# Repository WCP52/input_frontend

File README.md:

input_frontend
==============

Gain/Phase analyzer input frontend

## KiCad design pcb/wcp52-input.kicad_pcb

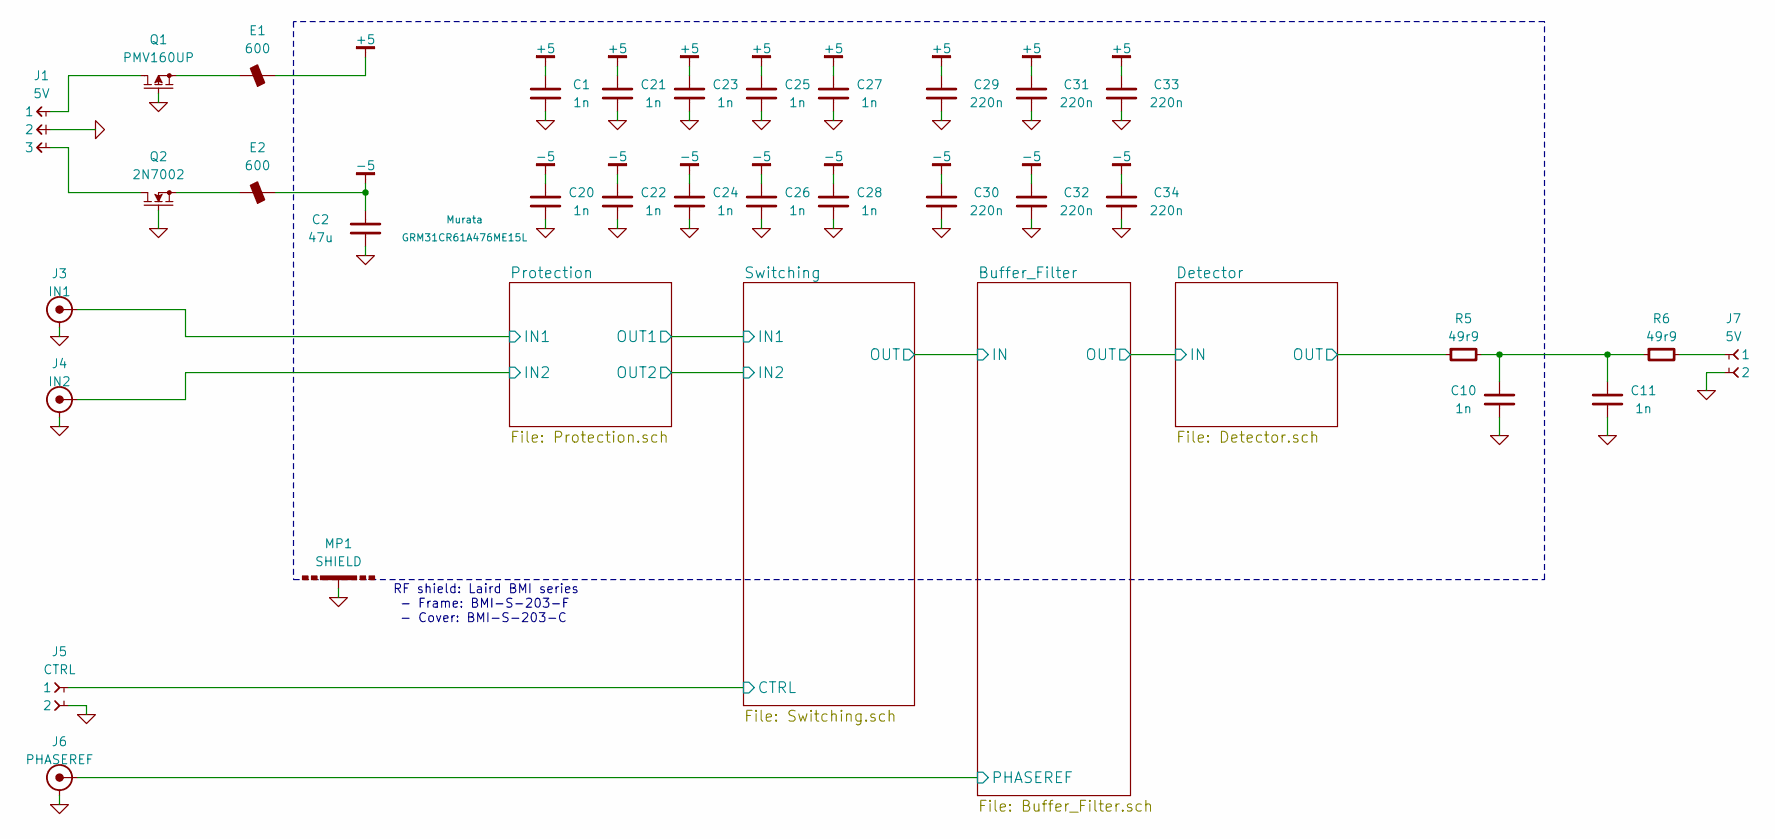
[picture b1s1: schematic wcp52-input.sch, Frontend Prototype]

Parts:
C1, C10, C11, C20, C21, C22, C23, C24, C25, C26, C27, C28: 1n; CAPC1005X55
C2: 47u; CAPC3216X70
C29, C30, C31, C32, C33, C34: 220n; CAPC2012X70
E1, E2: 600; INDC1005X60
J1: 5V; CONN_3-SIL
J3: IN1; CONN-2_CONSMA001
J4: IN2; CONN-2_CONSMA001
J5: CTRL; CONN_2-SIL
J6: PHASEREF; CONN-2_CONSMA001
J7: 5V; CONN_2-SIL
MP1: SHIELD
Q1: PMV160UP; SOT-23
Q2: 2N7002; SOT-23
R5, R6: 49r9; RESC1005X40

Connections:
+5: C1.1, C21.1, C23.1, C25.1, C27.1, C29.1, C31.1, C33.1, E1.2; also elsewhere on the board
-5: C2.1, C20.1, C22.1, C24.1, C26.1, C28.1, C30.1, C32.1, C34.1, E2.2; also elsewhere on the board
/Buffer_Filter/PHASEREF: J6.1; also elsewhere on the board
/Detector/OUT: R5.1; also elsewhere on the board
/Protection/IN1: J3.1; also elsewhere on the board
/Protection/IN2: J4.1; also elsewhere on the board
/Switching/CTRL: J5.1; also elsewhere on the board
GND: C1.2, C2.2, C10.2, C11.2, C20.2, C21.2, C22.2, C23.2, C24.2, C25.2, C26.2, C27.2, C28.2, C29.2, C30.2, C31.2, C32.2, C33.2, C34.2, J1.2, J3.2, J4.2, J5.2, J6.2, J7.2, MP1.1, Q1.1, Q2.1; also elsewhere on the board
unnamed: C10.1, C11.1, R5.2, R6.1
unnamed: E1.1, Q1.2
unnamed: E2.1, Q2.2
unnamed: J1.1, Q1.3
unnamed: J1.3, Q2.3
unnamed: J7.1, R6.2

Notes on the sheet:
RF shield: Laird BMI series - Frame: BMI-S-203-F - Cover: BMI-S-203-C

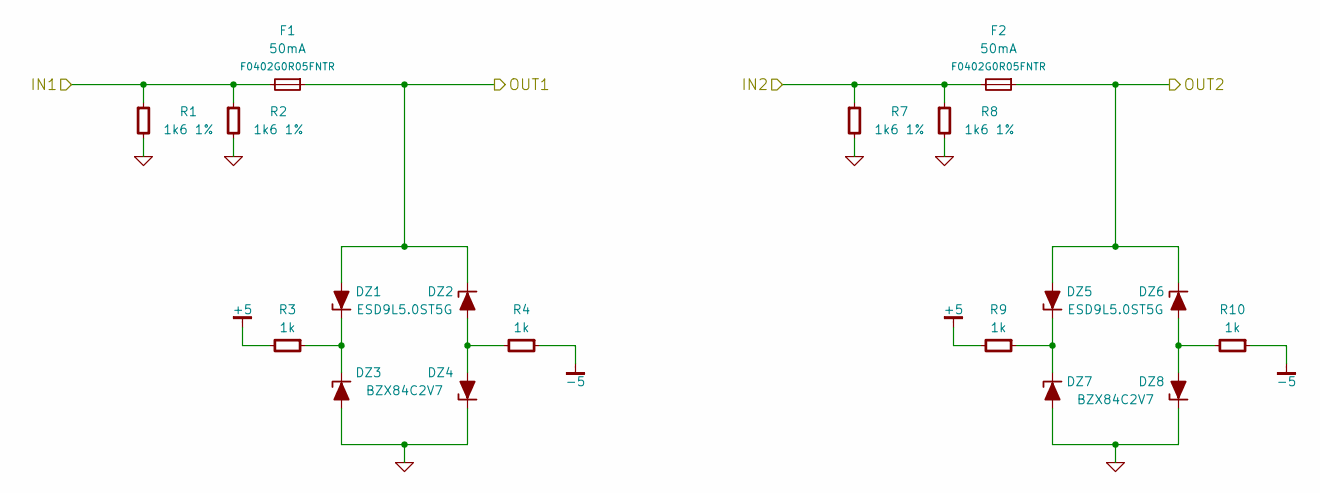
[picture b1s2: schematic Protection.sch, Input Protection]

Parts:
DZ1, DZ2, DZ5, DZ6: ESD9L5.0ST5G; SOD-923
DZ3, DZ4, DZ7, DZ8: BZX84C2V7; SOT-23
F1, F2: 50mA; RESC1005X40
R1, R2, R7, R8: 1k6 1%; RESC1005X40
R3, R4, R9, R10: 1k; RESC1005X40

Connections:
+5: R3.2, R9.2; also elsewhere on the board
-5: R4.1, R10.1; also elsewhere on the board
/Protection/IN1: F1.2, R1.1, R2.1; also elsewhere on the board
/Protection/IN2: F2.2, R7.1, R8.1; also elsewhere on the board
/Switching/IN1: DZ1.2, DZ2.1, F1.1; also elsewhere on the board
/Switching/IN2: DZ5.2, DZ6.1, F2.1; also elsewhere on the board
GND: DZ3.1, DZ4.3, DZ7.1, DZ8.3, R1.2, R2.2, R7.2, R8.2; also elsewhere on the board
unnamed: DZ1.1, DZ3.3, R3.1
unnamed: DZ2.2, DZ4.1, R4.2
unnamed: DZ5.1, DZ7.3, R9.1
unnamed: DZ6.2, DZ8.1, R10.2

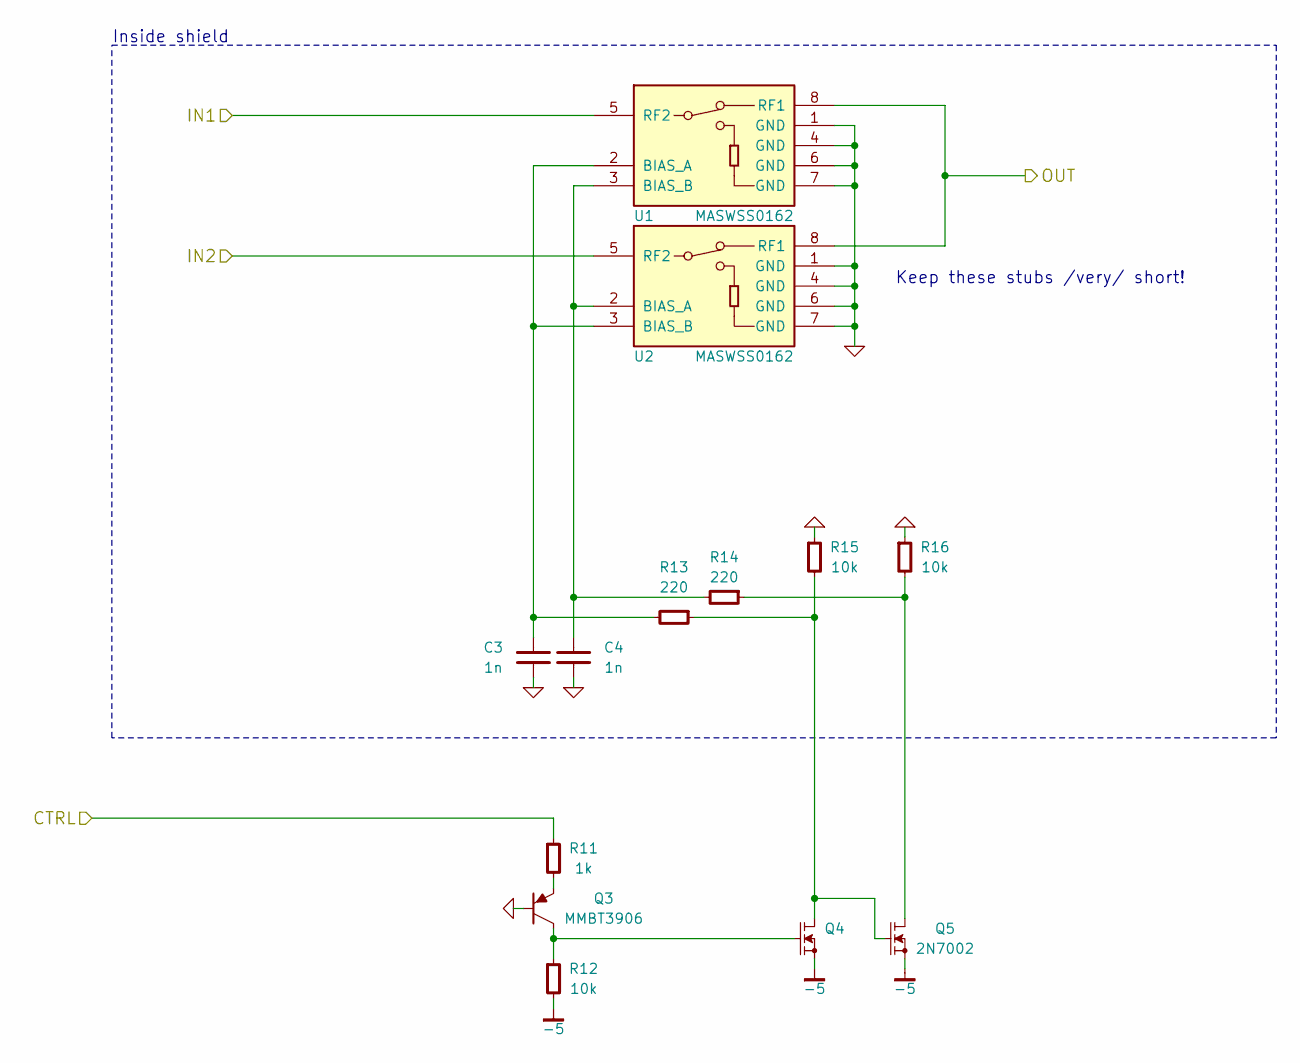
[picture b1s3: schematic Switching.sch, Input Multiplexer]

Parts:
C3, C4: 1n; CAPC1005X55
Q3: MMBT3906; SOT-23
Q4, Q5: 2N7002; SOT-23
R11: 1k; RESC1005X40
R12, R15, R16: 10k; RESC1005X40
R13, R14: 220; RESC1005X40
U1, U2: MASWSS0162; SOIC127P600X175-8

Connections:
-5: Q4.2, Q5.2, R12.2; also elsewhere on the board
/Buffer_Filter/IN: U1.8 (RF1), U2.8 (RF1); also elsewhere on the board
/Switching/CTRL: R11.1; also elsewhere on the board
/Switching/IN1: U1.5 (RF2); also elsewhere on the board
/Switching/IN2: U2.5 (RF2); also elsewhere on the board
GND: C3.2, C4.2, Q3.1, R15.1, R16.1, U1.1 (GND), U1.4 (GND), U1.6 (GND), U1.7 (GND), U2.1 (GND), U2.4 (GND), U2.6 (GND), U2.7 (GND); also elsewhere on the board
unnamed: C3.1, R13.2, U1.2 (BIAS_A), U2.3 (BIAS_B)
unnamed: C4.1, R14.2, U1.3 (BIAS_B), U2.2 (BIAS_A)
unnamed: Q3.2, R11.2
unnamed: Q3.3, Q4.1, R12.1
unnamed: Q4.3, Q5.1, R13.1, R15.2
unnamed: Q5.3, R14.1, R16.2

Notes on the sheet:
Keep these stubs /very/ short!
Inside shield

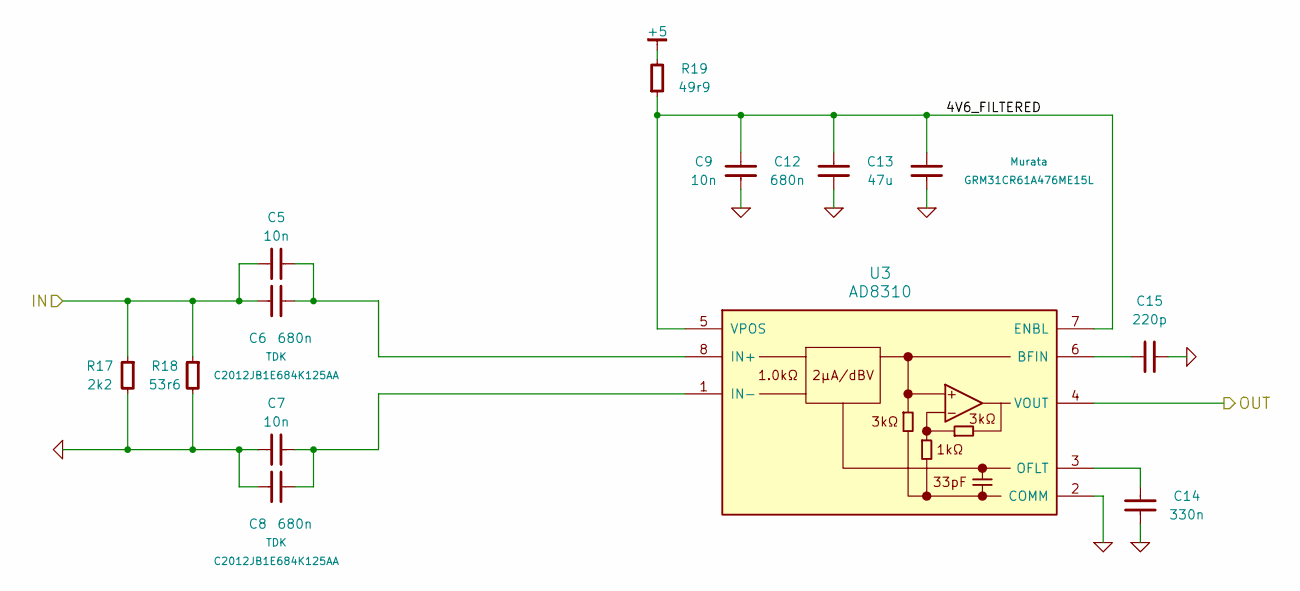
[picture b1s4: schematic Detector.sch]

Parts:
C5, C7, C9: 10n; CAPC1005X55
C6, C8, C12: 680n; CAPC2012X70
C13: 47u; CAPC3216X70
C14: 330n; CAPC1608X55
C15: 220p; CAPC1608X55
R17: 2k2; RESC1005X40
R18: 53r6; RESC1005X40
R19: 49r9; RESC1005X40
U3: AD8310; SOP65P490X109-8

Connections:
+5: R19.2; also elsewhere on the board
/Detector/4V6_FILTERED: C9.1, C12.2, C13.1, R19.1, U3.5 (VPOS), U3.7 (ENBL)
/Detector/IN: C5.1, C6.2, R17.1, R18.1; also elsewhere on the board
/Detector/OUT: U3.4 (VOUT); also elsewhere on the board
GND: C7.1, C8.2, C9.2, C12.1, C13.2, C14.2, C15.2, R17.2, R18.2, U3.2 (COMM); also elsewhere on the board
unnamed: C5.2, C6.1, U3.8 (IN+)
unnamed: C7.2, C8.1, U3.1 (IN-)
unnamed: C14.1, U3.3 (OFLT)
unnamed: C15.1, U3.6 (BFIN)

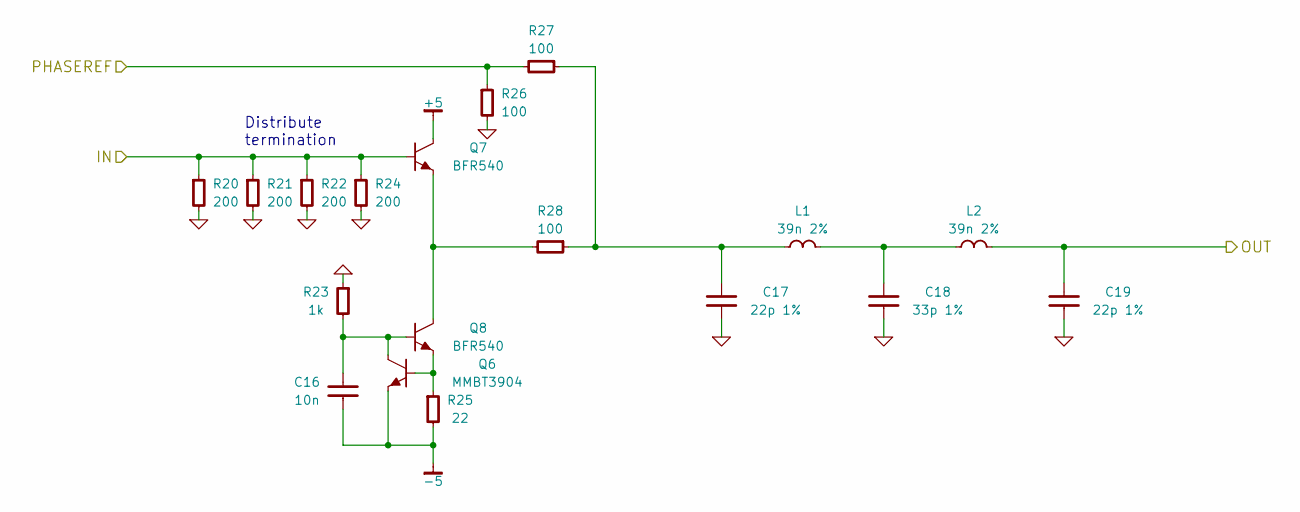
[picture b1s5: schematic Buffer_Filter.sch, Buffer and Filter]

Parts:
C16: 10n; CAPC1005X55
C17, C19: 22p 1%; CAPC1608X55
C18: 33p 1%; CAPC1608X55
L1, L2: 39n 2%; INDC1005X60
Q6: MMBT3904; SOT-23
Q7, Q8: BFR540; SOT-23
R20, R21, R22, R24: 200; RESC1005X40
R23: 1k; RESC1005X40
R25: 22; RESC1005X40
R26, R27, R28: 100; RESC1005X40

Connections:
+5: Q7.3; also elsewhere on the board
-5: C16.2, Q6.2, R25.2; also elsewhere on the board
/Buffer_Filter/IN: Q7.1, R20.1, R21.1, R22.1, R24.1; also elsewhere on the board
/Buffer_Filter/PHASEREF: R26.1, R27.2; also elsewhere on the board
/Detector/IN: C19.1, L2.1; also elsewhere on the board
GND: C17.2, C18.2, C19.2, R20.2, R21.2, R22.2, R23.1, R24.2, R26.2; also elsewhere on the board
unnamed: C16.1, Q6.3, Q8.1, R23.2
unnamed: C17.1, L1.2, R27.1, R28.1
unnamed: C18.1, L1.1, L2.2
unnamed: Q6.1, Q8.2, R25.1
unnamed: Q7.2, Q8.3, R28.2

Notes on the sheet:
Distribute termination

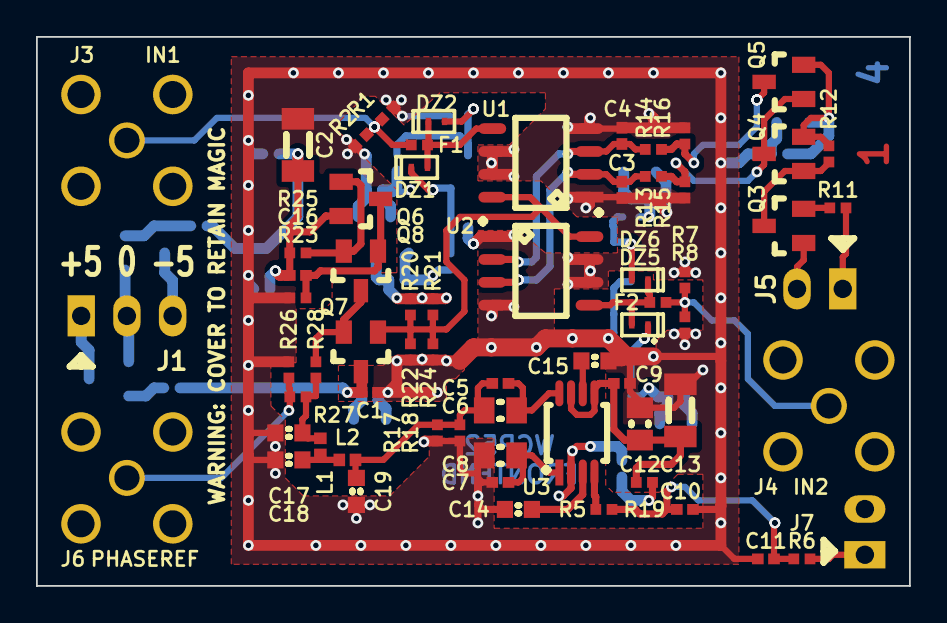
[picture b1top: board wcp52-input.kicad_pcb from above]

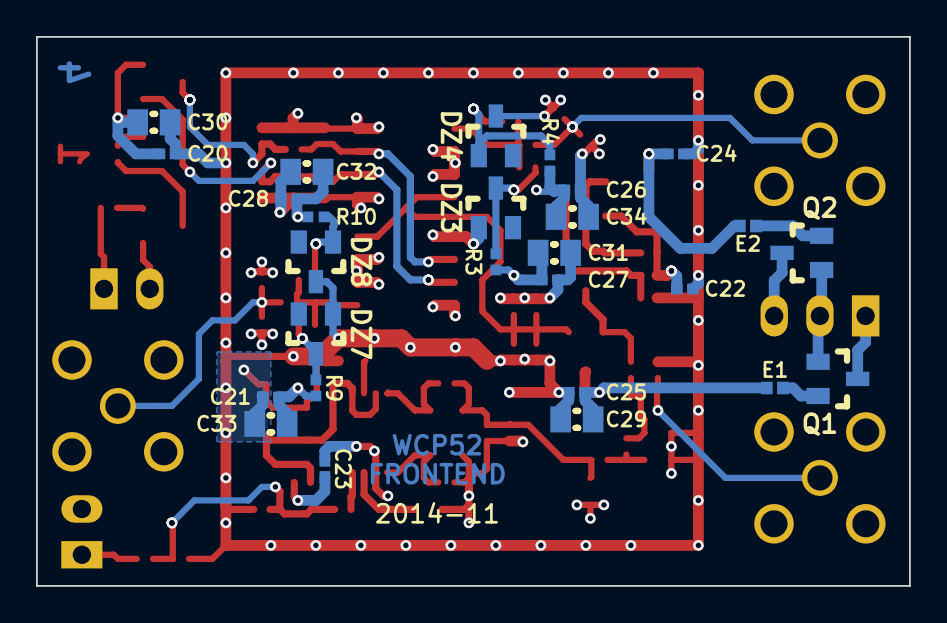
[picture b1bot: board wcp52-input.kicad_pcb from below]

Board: 4 copper layers, 48.5 x 30.5 mm, 93 parts (27 on the bottom side), 38 nets.

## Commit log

2014-11-09 Checked in schematic files from other repos
2014-11-09 Renamed 'detector' project to 'input frontend'
2014-11-09 Replaced clamping diode placeholders
2014-11-09 Configured PCB
2014-11-09 Added shield pad
2014-11-09 Specified part for C14
    U# (AD8310) offset filter capacitor
2014-11-09 Associated parts with footprints
2014-11-09 Routed PCB
2014-11-09 Rearranged - smaller PCB
2014-11-10 PCB tweaks
2014-11-10 Added postprocessing scripts
2014-11-11 Corrected postprocessing scripts
2014-11-11 Brought in new scripts from synth
2014-11-11 Added 3D renders
2014-11-11 Corrected internal planes
    Controlled-impedance trace on back of board to J4 must be backed by
    ground, not +5
2014-11-11 Added more decoupling
2014-11-11 More postprocessing script adjustments
2014-11-11 Corrected schematic page sizes
2014-11-11 Adjusted filter for proper Chebyshev response
2014-11-11 Removed ground under filter
    Minimize error from stray capacitance
2014-11-12 Rearranged to fit visible refdes
2014-11-12 How'd the schematic revert back to the old one?
    *grumble*
2014-11-12 Added new schematic renders - will postprocess remotely
2014-11-12 Postprocessing
2014-11-14 Switched to PTH SMA connectors
2014-11-14 Minor silkscreen fixes
2014-11-17 Updated MOSFET types
2014-11-29 Updated schematic renders
